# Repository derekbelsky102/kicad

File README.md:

Kicad cheetsheet: https://silica.io/wp-content/uploads/2018/06/kicad-cheatsheet-landscape.pdf

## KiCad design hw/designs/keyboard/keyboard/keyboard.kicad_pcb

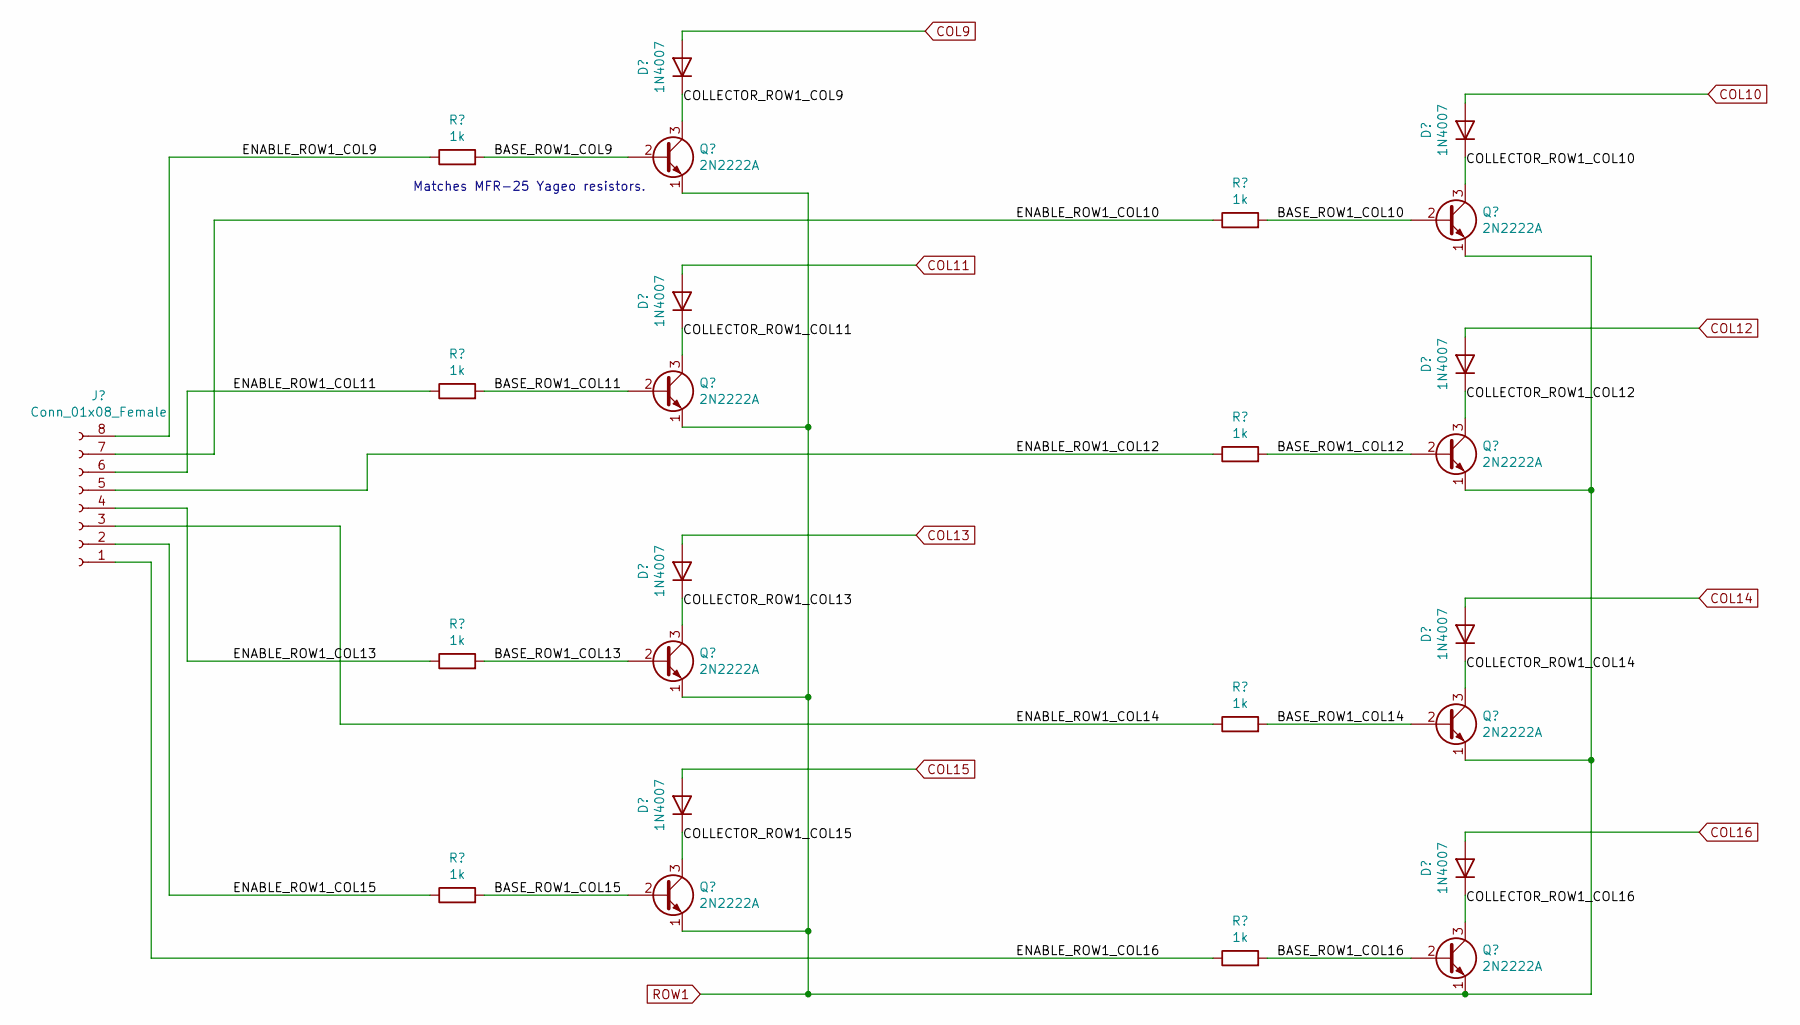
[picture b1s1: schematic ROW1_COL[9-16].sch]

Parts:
D9, D10, D11, D12, D13, D14, D15, D16: 1N4007; D_DO-41_SOD81_P10.16mm_Horizontal
J2: Conn_01x08_Female; PinSocket_1x08_P2.54mm_Vertical
Q9, Q10, Q11, Q12, Q13, Q14, Q15, Q16: 2N2222A; TO-92_Inline
R9, R10, R11, R12, R13, R14, R15, R16: 1k; R_Axial_DIN0207_L6.3mm_D2.5mm_P10.16mm_Horizontal

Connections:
/ROW1_COL[9-16]/BASE_ROW1_COL9: Q9.2 (B), R9.2
/ROW1_COL[9-16]/BASE_ROW1_COL10: Q13.2 (B), R13.2
/ROW1_COL[9-16]/BASE_ROW1_COL11: Q10.2 (B), R10.2
/ROW1_COL[9-16]/BASE_ROW1_COL12: Q14.2 (B), R14.2
/ROW1_COL[9-16]/BASE_ROW1_COL13: Q11.2 (B), R11.2
/ROW1_COL[9-16]/BASE_ROW1_COL14: Q15.2 (B), R15.2
/ROW1_COL[9-16]/BASE_ROW1_COL15: Q12.2 (B), R12.2
/ROW1_COL[9-16]/BASE_ROW1_COL16: Q16.2 (B), R16.2
/ROW1_COL[9-16]/COLLECTOR_ROW1_COL9: D9.1 (K), Q9.3 (C)
/ROW1_COL[9-16]/COLLECTOR_ROW1_COL10: D13.1 (K), Q13.3 (C)
/ROW1_COL[9-16]/COLLECTOR_ROW1_COL11: D10.1 (K), Q10.3 (C)
/ROW1_COL[9-16]/COLLECTOR_ROW1_COL12: D14.1 (K), Q14.3 (C)
/ROW1_COL[9-16]/COLLECTOR_ROW1_COL13: D11.1 (K), Q11.3 (C)
/ROW1_COL[9-16]/COLLECTOR_ROW1_COL14: D15.1 (K), Q15.3 (C)
/ROW1_COL[9-16]/COLLECTOR_ROW1_COL15: D12.1 (K), Q12.3 (C)
/ROW1_COL[9-16]/COLLECTOR_ROW1_COL16: D16.1 (K), Q16.3 (C)
/ROW1_COL[9-16]/ENABLE_ROW1_COL9: J2.8, R9.1
/ROW1_COL[9-16]/ENABLE_ROW1_COL10: J2.7, R13.1
/ROW1_COL[9-16]/ENABLE_ROW1_COL11: J2.6, R10.1
/ROW1_COL[9-16]/ENABLE_ROW1_COL12: J2.5, R14.1
/ROW1_COL[9-16]/ENABLE_ROW1_COL13: J2.4, R11.1
/ROW1_COL[9-16]/ENABLE_ROW1_COL14: J2.3, R15.1
/ROW1_COL[9-16]/ENABLE_ROW1_COL15: J2.2, R12.1
/ROW1_COL[9-16]/ENABLE_ROW1_COL16: J2.1, R16.1
COL9: D9.2 (A)
COL10: D13.2 (A)
COL11: D10.2 (A)
COL12: D14.2 (A)
COL13: D11.2 (A)
COL14: D15.2 (A)
COL15: D12.2 (A)
COL16: D16.2 (A)
ROW1: Q9.1 (E), Q10.1 (E), Q11.1 (E), Q12.1 (E), Q13.1 (E), Q14.1 (E), Q15.1 (E), Q16.1 (E); also elsewhere on the board

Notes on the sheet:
Matches MFR-25 Yageo resistors.

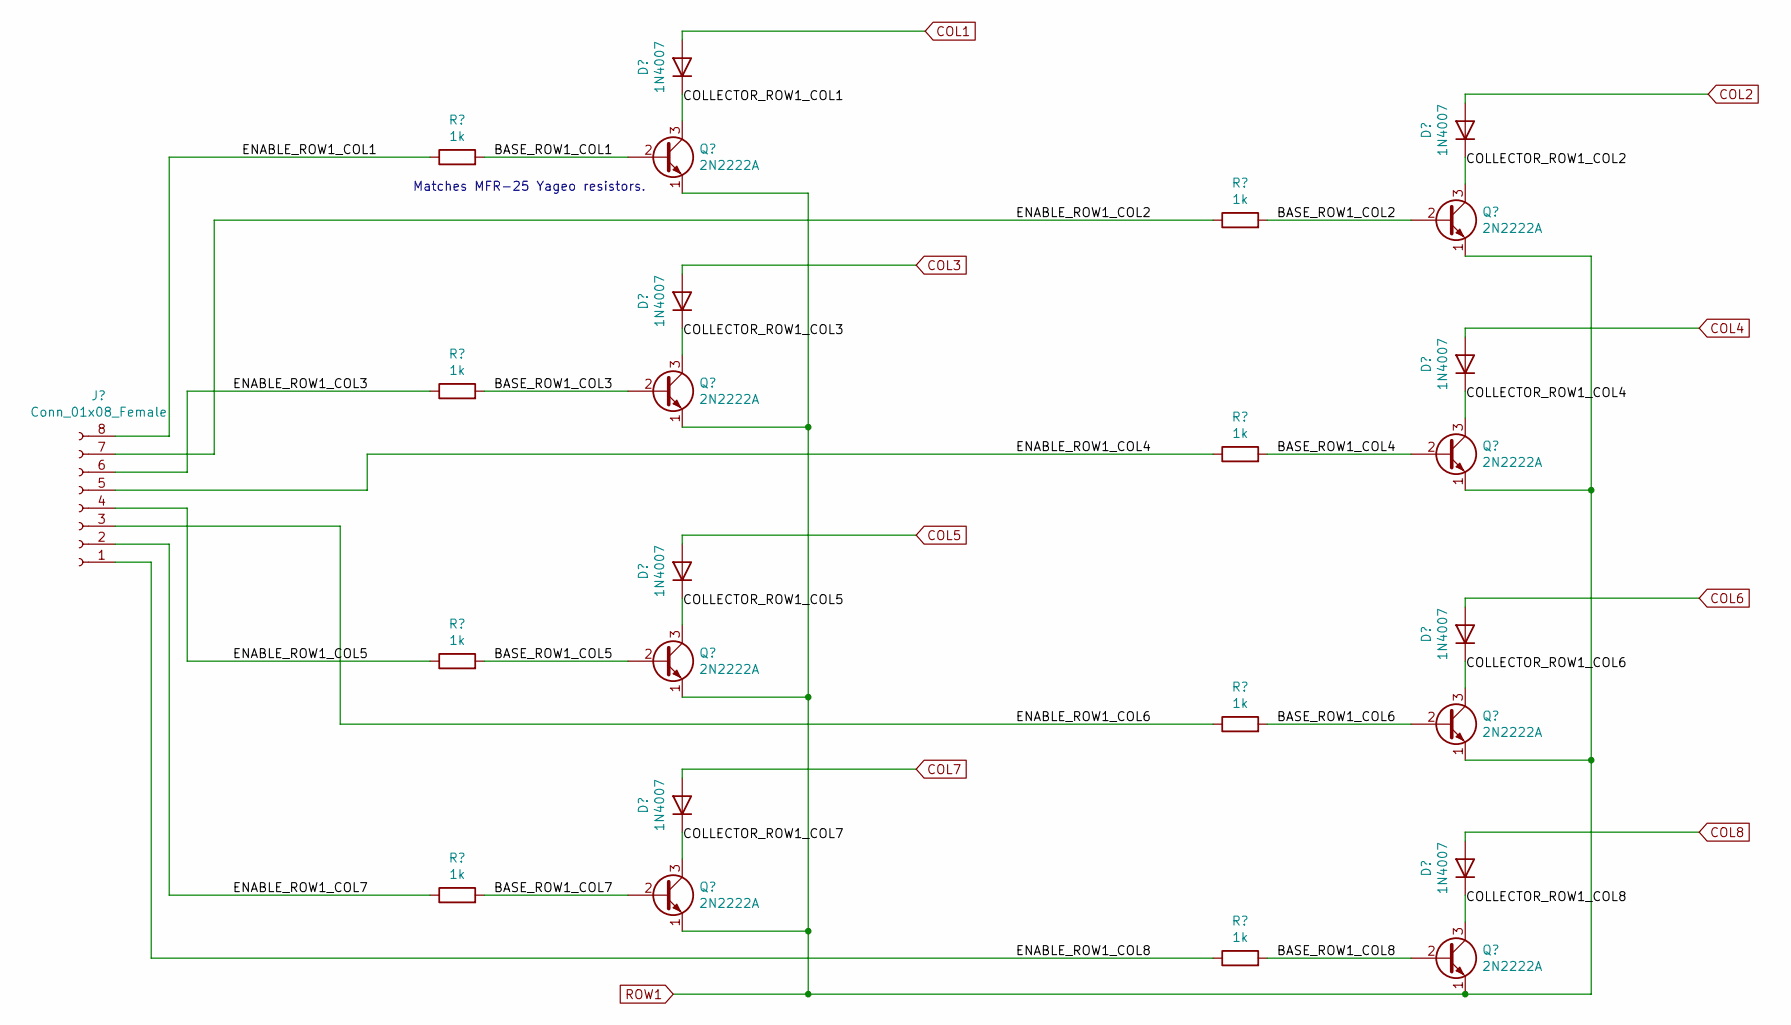
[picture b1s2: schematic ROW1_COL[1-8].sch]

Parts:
D1, D2, D3, D4, D5, D6, D7, D8: 1N4007; D_DO-41_SOD81_P10.16mm_Horizontal
J1: Conn_01x08_Female; PinSocket_1x08_P2.54mm_Vertical
Q1, Q2, Q3, Q4, Q5, Q6, Q7, Q8: 2N2222A; TO-92_Inline
R1, R2, R3, R4, R5, R6, R7, R8: 1k; R_Axial_DIN0207_L6.3mm_D2.5mm_P10.16mm_Horizontal

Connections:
/ROW1_COL[1-8]/BASE_ROW1_COL1: Q1.2 (B), R1.2
/ROW1_COL[1-8]/BASE_ROW1_COL2: Q5.2 (B), R5.2
/ROW1_COL[1-8]/BASE_ROW1_COL3: Q2.2 (B), R2.2
/ROW1_COL[1-8]/BASE_ROW1_COL4: Q6.2 (B), R6.2
/ROW1_COL[1-8]/BASE_ROW1_COL5: Q3.2 (B), R3.2
/ROW1_COL[1-8]/BASE_ROW1_COL6: Q7.2 (B), R7.2
/ROW1_COL[1-8]/BASE_ROW1_COL7: Q4.2 (B), R4.2
/ROW1_COL[1-8]/BASE_ROW1_COL8: Q8.2 (B), R8.2
/ROW1_COL[1-8]/COLLECTOR_ROW1_COL1: D1.1 (K), Q1.3 (C)
/ROW1_COL[1-8]/COLLECTOR_ROW1_COL2: D5.1 (K), Q5.3 (C)
/ROW1_COL[1-8]/COLLECTOR_ROW1_COL3: D2.1 (K), Q2.3 (C)
/ROW1_COL[1-8]/COLLECTOR_ROW1_COL4: D6.1 (K), Q6.3 (C)
/ROW1_COL[1-8]/COLLECTOR_ROW1_COL5: D3.1 (K), Q3.3 (C)
/ROW1_COL[1-8]/COLLECTOR_ROW1_COL6: D7.1 (K), Q7.3 (C)
/ROW1_COL[1-8]/COLLECTOR_ROW1_COL7: D4.1 (K), Q4.3 (C)
/ROW1_COL[1-8]/COLLECTOR_ROW1_COL8: D8.1 (K), Q8.3 (C)
/ROW1_COL[1-8]/ENABLE_ROW1_COL1: J1.8, R1.1
/ROW1_COL[1-8]/ENABLE_ROW1_COL2: J1.7, R5.1
/ROW1_COL[1-8]/ENABLE_ROW1_COL3: J1.6, R2.1
/ROW1_COL[1-8]/ENABLE_ROW1_COL4: J1.5, R6.1
/ROW1_COL[1-8]/ENABLE_ROW1_COL5: J1.4, R3.1
/ROW1_COL[1-8]/ENABLE_ROW1_COL6: J1.3, R7.1
/ROW1_COL[1-8]/ENABLE_ROW1_COL7: J1.2, R4.1
/ROW1_COL[1-8]/ENABLE_ROW1_COL8: J1.1, R8.1
COL1: D1.2 (A)
COL2: D5.2 (A)
COL3: D2.2 (A)
COL4: D6.2 (A)
COL5: D3.2 (A)
COL6: D7.2 (A)
COL7: D4.2 (A)
COL8: D8.2 (A)
ROW1: Q1.1 (E), Q2.1 (E), Q3.1 (E), Q4.1 (E), Q5.1 (E), Q6.1 (E), Q7.1 (E), Q8.1 (E); also elsewhere on the board

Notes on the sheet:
Matches MFR-25 Yageo resistors.

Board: 2 copper layers, 50 parts (0 on the bottom side), 49 nets, no tracks yet.

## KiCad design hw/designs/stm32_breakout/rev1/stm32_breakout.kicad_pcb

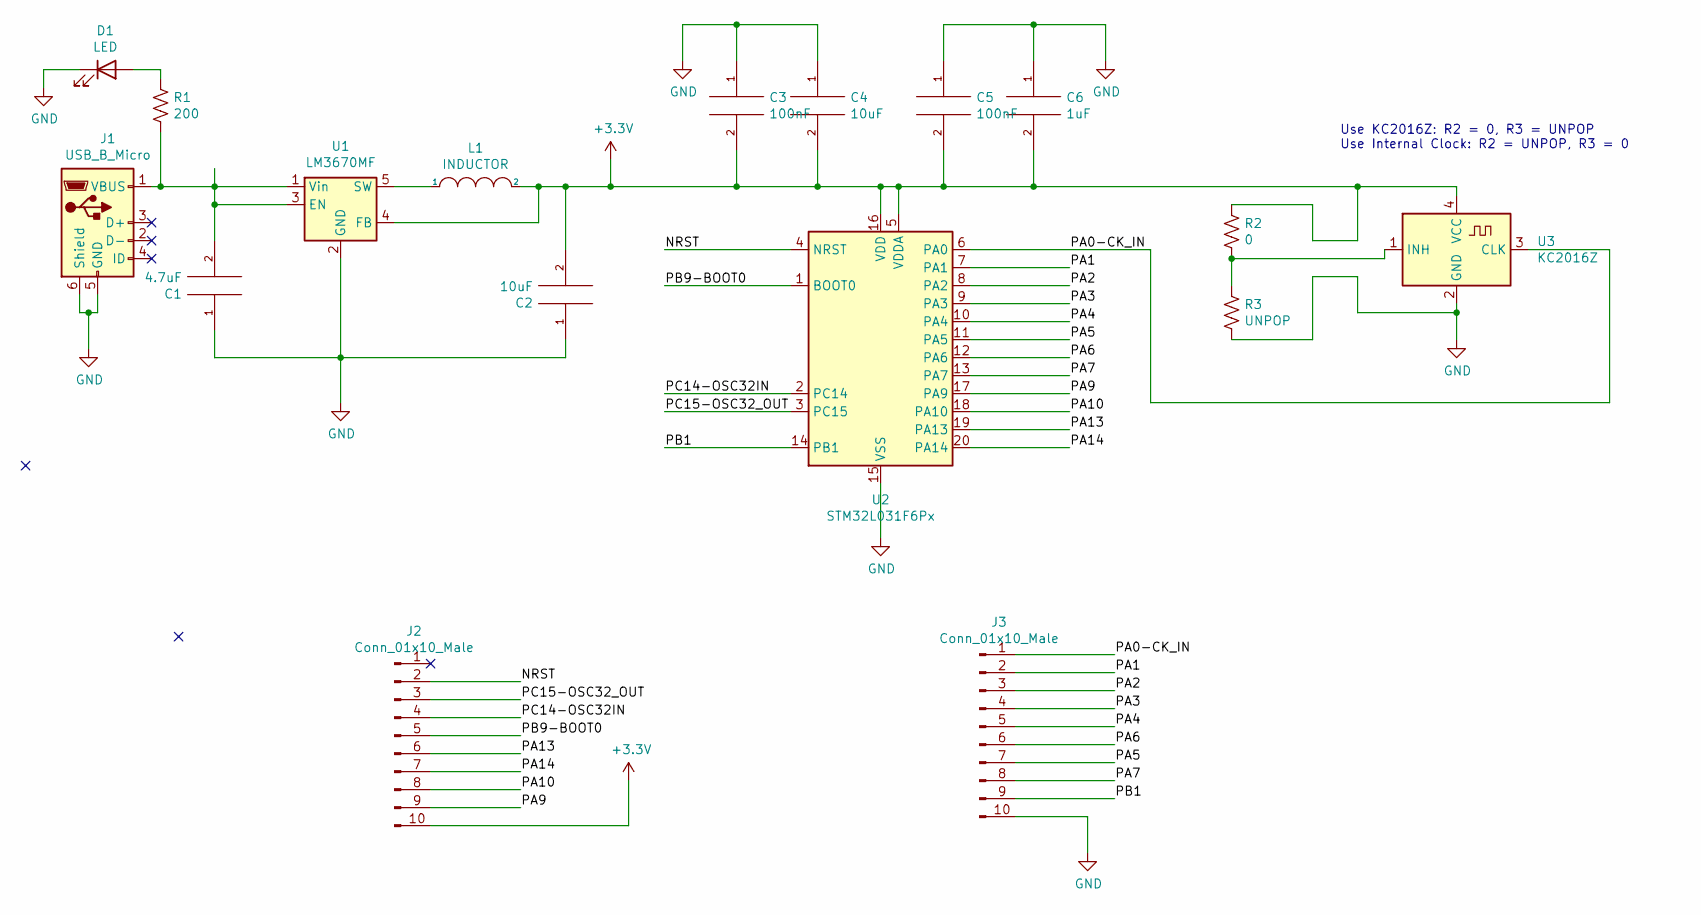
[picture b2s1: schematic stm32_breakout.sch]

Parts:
C1: 4.7uF; C_0805_2012Metric
C2, C4: 10uF; C_0805_2012Metric
C3, C5: 100nF; C_0805_2012Metric
C6: 1uF; C_0805_2012Metric
D1: LED; LED_0805_2012Metric
J1: USB_B_Micro; USB_Micro-B_Molex_47346-0001
J2, J3: Conn_01x10_Male; PinSocket_1x10_P2.54mm_Vertical
L1: INDUCTOR; L_1210_3225Metric_Pad1.42x2.65mm_HandSolder
R1: 200; R_0805_2012Metric
R2: 0; R_0805_2012Metric
R3: UNPOP; R_0805_2012Metric
U1: LM3670MF; TSOT-23-5
U2: STM32L031F6Px; TSSOP-20_4.4x6.5mm_P0.65mm
U3: KC2016Z

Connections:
+3V3: C2.2, C3.2, C4.2, C5.2, C6.2, J2.10, L1.2, R2.1, U1.4 (FB), U2.5 (VDDA), U2.16 (VDD), U3.4 (VCC)
/NRST: J2.2, U2.4 (NRST)
/PA0-CK_IN: J3.1, U2.6 (PA0), U3.3 (CLK)
/PA1: J3.2, U2.7 (PA1)
/PA2: J3.3, U2.8 (PA2)
/PA3: J3.4, U2.9 (PA3)
/PA4: J3.5, U2.10 (PA4)
/PA5: J3.7, U2.11 (PA5)
/PA6: J3.6, U2.12 (PA6)
/PA7: J3.8, U2.13 (PA7)
/PA9: J2.9, U2.17 (PA9)
/PA10: J2.8, U2.18 (PA10)
/PA13: J2.6, U2.19 (PA13)
/PA14: J2.7, U2.20 (PA14)
/PB1: J3.9, U2.14 (PB1)
/PB9-BOOT0: J2.5, U2.1 (BOOT0)
/PC14-OSC32IN: J2.4, U2.2 (PC14)
/PC15-OSC32_OUT: J2.3, U2.3 (PC15)
GND: C1.1, C2.1, C3.1, C4.1, C5.1, C6.1, D1.1 (K), J1.5 (GND), J1.6 (Shield), J3.10, R3.2, U1.2 (GND), U2.15 (VSS), U3.2 (GND)
unnamed: C1.2, J1.1 (VBUS), R1.2, U1.1 (Vin), U1.3 (EN)
unnamed: D1.2 (A), R1.1
unnamed: L1.1, U1.5 (SW)
unnamed: R2.2, R3.1, U3.1 (INH)

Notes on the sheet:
Use KC2016Z: R2 = 0, R3 = UNPOP Use Internal Clock: R2 = UNPOP, R3 = 0

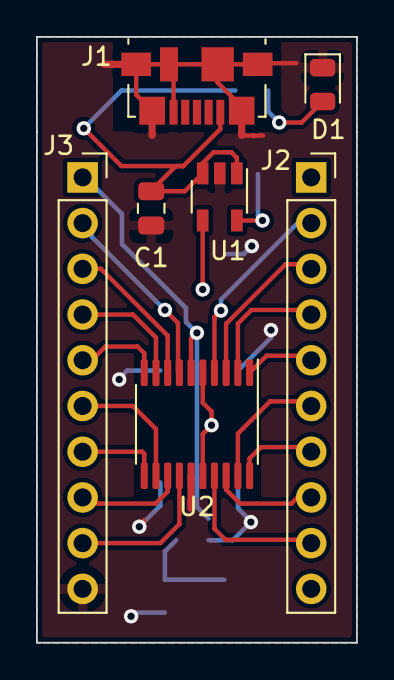
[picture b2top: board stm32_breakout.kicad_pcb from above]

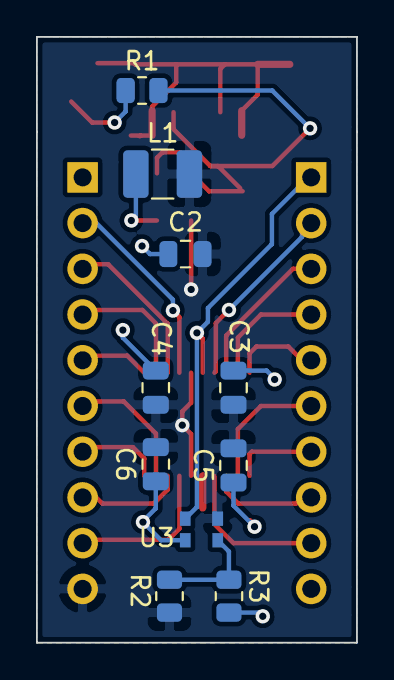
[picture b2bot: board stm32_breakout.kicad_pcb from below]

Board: 2 copper layers, 17.8 x 33.7 mm, 17 parts (10 on the bottom side), 23 nets.

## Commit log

2021-04-02 Completed video 1 of the tutorial
2021-04-02 Added pull down resistors. Now video 1 is complete
2021-04-17 Updated tutorials
2021-04-17 Updating File Structure
2021-04-19 Initial schematic
2021-04-22 Added clocking and jumpers
2021-04-25 Updated to 32K flash and replaced resistor with jumper. Also added Nucleo reference material
2021-04-25 Added bypass caps to the voltage regulator.
2021-05-05 Added LED, annotated schematic, and ERC is passing
2021-05-05 All parts except KC2016Z are associated with footprints now
2021-05-30 Added KC2016 footprint
2021-05-30 Started routing. Some changes will need to be made to schematic
2021-05-31 Removed RTC circuit. Changed pinout on headers. Updated jumpers to resistors instead. Started routing
2021-05-31 Routing complete except for 3V3 and GND
2021-05-31 Board is complete. Needs review
2021-05-31 Just pushing in case some changes didn't make it in
2021-05-31 Attempt to switch the pinout of the regulator part. Made a new project specific library called Adek lib
2021-05-31 Updated PCB to address SOT223R part change
2021-07-11 Moving everything to rev0 because another rev will be needed
2021-07-13 Added fab outputs
2021-09-12 Added a git ignore file after a brief search for one for kicad projects. It looks like it should do the trick for now.
2021-09-12 untrack files in kicad.gitignore. Please see the stack overflow post that I link below if you are still having issues with ignored files showing up. Most likely running the commands in the linked sta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
2021-09-12 tried to add part links and data sheets but my gitignore doesn't seem to be working
2021-09-26 Updated with SWD pins
2021-09-26 Add README with versions
2021-09-26 Moving files to tssop20 folder
2021-09-27 Started new schematic with LQFP-32 part
2021-10-07 Updated with 13 pin connector and 10pin SWD connector.
2021-10-07 Updated some part numbers
2021-10-27 Updated with BOM and PDF folders
2021-10-27 Updated KC2016Z and part for 10 pin header
2021-10-27 Updated KC2016Z part but didn't push in last commit
2021-10-27 Part number was missing for inductor
2021-10-27 Updated BOM with inductor part
2021-11-04 Adding symbols for another design
2022-11-20 One page of schematic
2022-11-22 Adding sheets
